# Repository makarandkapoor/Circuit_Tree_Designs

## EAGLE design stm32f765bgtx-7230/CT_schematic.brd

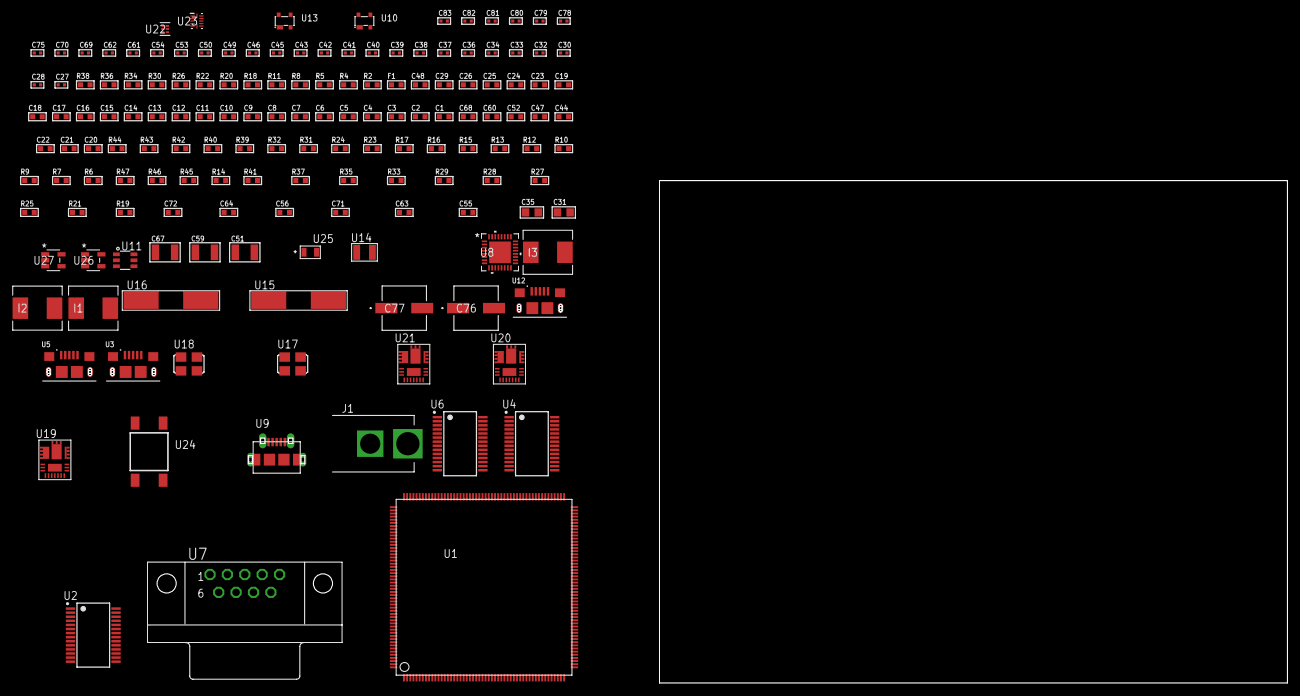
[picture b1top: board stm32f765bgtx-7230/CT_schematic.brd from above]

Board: 2 copper layers, 154 parts (0 on the bottom side), 116 nets, no tracks yet.

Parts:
C1, C24, C29, C48: 1e-06; C0603
C2, C3, C4, C5, C6, C7, C8, C9, C10, C11, C12, C13, C14, C15, C16, C17, C18, C19, C25, C26: 1e-07; C0603
C20: 4.7e-06; C0603
C21, C22, C44, C47, C52, C60, C68: 2.2e-06; C0603
C23: 1e-08; C0603
C27, C28: 1e-11; C0402
C30, C32, C33, C34, C36, C37, C38, C39, C40, C41, C42, C43, C45, C46, C53, C54, C61, C62, C69, C70, C75, C79, C81: 1e-07; C0402
C31, C35: 4.7e-06; C0805
C49, C50, C78, C80, C82, C83: 1e-08; C0402
C51, C59, C67: 0.0001; C1210
C55, C63, C71: 8.5935703950126e-09; R0603
C56, C64, C72: 2.929626271027e-07; R0603
C76, C77: 0.0001; EXV-9H
F1: 240.0; L0603
I1, I2, I3: 6.8e-07; IND25X25CZ
J1: PJ-037B; PJ-037B_PACKAGE
R2: 1000.0; R0603
R4, R5, R8, R11: 4700.0; R0603
R6, R7, R9, R10, R12, R13, R16, R17, R42, R43: 10000.0; R0603
R14: 100000.0; R0603
R15: 47000.0; R0603
R18, R26, R34: 0.1; R0603
R19, R27, R35: 4030.2416170974; R0603
R20: 1600.0; R0603
R21, R29, R37: 59.319518072289; R0603
R22, R30, R38: 130.0; R0603
R23, R31, R39: 39000.0; R0603
R24, R32, R40: 49900.0; R0603
R25, R33, R41: 5216.2133333333; R0603
R28: 719.68600305311; R0603
R36: 453.0; R0603
R44: 82000.0; R0603
R45: 300000.0; R0603
R46: 120000.0; R0603
R47: 200000.0; R0603
U1: STM32F765BGT6; LQFP208
U2, U4: FT232RL-REEL; SSOP-28
U3, U5, U12: 10118193-0001LF; FCI_10118193-0001LF
U6: ST3241EBPR; SSOP-28
U7: 182-009-113R531; 182-009-MALE
U8: TUSB1210BRHBR; RHB32_3P45X3P45
U9: 47590-0001; MICRO_USB_AB
U10, U13: prtr5v0u2ax; SOT143B
U11: MAX4995AAUT+T; SOT-23-6
U14: ABS07-32.768KHZ-7-T
U15, U16: ABLS-12.000MHZ-B4-T
U17: ASFL1-19.2MHZ-NCS; ASFL1
U18: ASFL1-25MHZ-NCS; ASFL1
U19, U20, U21: IR3899MTR1PBF
U22: TPS3895ADRYR; SON-6
U23: LSF0204DRUTR; RUT0012A
U24: 4-1437565-2; SW_4-1437565-2
U25: Q65110A2395; LGM67K-G1J2-24-Z
U26, U27: nc7sz125m5x; NC7SZ125M5X

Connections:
CLK_CRYSTAL_U1_9: C27.1, U1.9, U14.1
CLK_CRYSTAL_U1_10: C28.1, U1.10, U14.2
CLK_CRYSTAL_U2_27: U2.27, U15.1
CLK_CRYSTAL_U2_28: U2.28, U15.2
CLK_CRYSTAL_U4_27: U4.27, U16.1
CLK_CRYSTAL_U4_28: U4.28, U16.2
CLK_U1_32: U1.32, U18.3
CLK_U8_1: U8.1, U17.3
GND: C1.2, C2.2, C3.2, C4.2, C5.2, C6.2, C7.2, C8.2, C9.2, C10.2, C11.2, C12.2, C13.2, C14.2, C15.2, C16.2, C17.2, C18.2, C19.2, C20.2, C21.2, C22.2, C23.2, C24.2, C25.2, C26.2, C27.2, C28.2, C29.2, C30.2, C31.2, C32.2, C33.2, C34.2, C35.2, C36.2, C37.2, C38.2, C41.2, C42.2, C43.2, C44.2, C45.2, C46.2, C47.2, C48.2, C49.2, C50.2, C52.2, C53.2, C54.2, C60.2, C61.2, C62.2, C68.2, C69.2, C70.2, C75.2, C76.2, C77.2, C78.2, C79.2, C80.2, C81.2, C82.2, C83.2, J1.2, R2.2, R6.2, R10.2, R13.2, R15.2, R17.2, R18.1, R18.2, R20.2, R23.2, R25.2, R26.1, R26.2, R28.2, R31.2, R33.2, R34.1, R34.2, R36.2, R39.2, R41.2, R44.2, R46.2, U1.14, U1.25, U1.40, U1.51, U1.60, U1.72, U1.82, U1.93, U1.114, U1.125, U1.136, U1.145, U1.149, U1.170, U1.184, U1.202, U2.7, U2.18, U2.21, U2.25, U2.26, U3.5, U3.6, U3.7, U3.8, U3.9, U4.7, U4.18, U4.21, U4.25, U4.26, U5.5, U5.6, U5.7, U5.8, U5.9, U6.23, U6.25, U7.5, U8.33, U9.5, U9.6, U9.7, U9.8, U9.9, U10.1, U11.2, U12.5, U12.6, U12.7, U12.8, U12.9, U13.1, U17.2, U18.2, U19.4, U19.11, U19.17, U20.4, U20.11, U20.17, U21.4, U21.11, U21.17, U22.2, U23.6, U25.C, U26.1, U26.3, U27.1, U27.3
NET_U1_34: R4.1, U1.34, U26.4
NET_U1_42: C23.1, C24.1, F1.1, U1.41, U1.42
NET_U1_92: C21.1, U1.92
NET_U1_148: C22.1, U1.148
NET_U1_197: R6.1, U1.197
NET_U1_203: R7.1, U1.203
NET_U1_208: U24.3, U24.4
NET_U2_14: R9.1, U2.14
NET_U2_17: C32.1, U2.17
NET_U2_19: R10.1, U2.19
NET_U3_1: R8.1, U3.1
NET_U3_2: U2.16, U3.2
NET_U3_3: U2.15, U3.3
NET_U4_14: R12.1, U4.14
NET_U4_17: C36.1, U4.17
NET_U4_19: R13.1, U4.19
NET_U5_1: R11.1, U5.1
NET_U5_2: U4.16, U5.2
NET_U5_3: U4.15, U5.3
NET_U6_1: C40.1, U6.1
NET_U6_2: C40.2, U6.2
NET_U6_3: C42.1, U6.3
NET_U6_22: R14.1, U6.22
NET_U6_24: C39.2, U6.24
NET_U6_27: C41.1, U6.27
NET_U6_28: C39.1, U6.28
NET_U7_2: U6.4, U7.2
NET_U7_3: U6.9, U7.3
NET_U7_7: U6.5, U7.7
NET_U7_8: U6.10, U7.8
NET_U8_11: R16.1, U8.11
NET_U8_12: C47.1, U8.12
NET_U8_14: R17.1, U8.14
NET_U8_20: C44.1, U8.20
NET_U8_27: R5.1, U8.27, U27.4
NET_U9_1: C48.1, U8.22, U9.1, U10.4, U11.1
NET_U9_2: U8.19, U9.2, U10.3
NET_U9_3: U8.18, U9.3, U10.2
NET_U9_4: U8.23, U9.4
NET_U11_3: R15.1, U11.3
NET_U11_4: U8.17, U11.4
NET_U19_1: C55.1, R19.1, R20.1, R21.1, R22.1, U19.1, U19.8
NET_U19_2: C54.1, U19.2
NET_U19_3: C55.2, C56.1, C56.2, U19.3
NET_U19_5: R23.1, U19.5
NET_U19_10: C52.1, U19.10
NET_U19_12: C51.1, I1.1, U19.12
NET_U19_14: C51.2, U19.14
NET_U19_15: R24.1, R25.1, U19.15
NET_U19_ATNET_3: I1.2, R19.2
NET_U19_ATNET_4: C56.2, R21.2
NET_U20_1: C63.1, R27.1, R28.1, R29.1, R30.1, U20.1, U20.8
NET_U20_2: C62.1, U20.2
NET_U20_3: C63.2, C64.1, C64.2, U20.3
NET_U20_5: R31.1, U20.5
NET_U20_10: C60.1, U20.10
NET_U20_12: C59.1, I2.1, U20.12
NET_U20_14: C59.2, U20.14
NET_U20_15: R32.1, R33.1, U20.15
NET_U20_ATNET_3: I2.2, R27.2
NET_U20_ATNET_4: C64.2, R29.2
NET_U21_1: C71.1, R35.1, R36.1, R37.1, R38.1, U21.1, U21.8
NET_U21_2: C70.1, U21.2
NET_U21_3: C71.2, C72.1, C72.2, U21.3
NET_U21_5: R39.1, U21.5
NET_U21_10: C68.1, U21.10
NET_U21_12: C67.1, I3.1, U21.12
NET_U21_14: C67.2, U21.14
NET_U21_15: R40.1, R41.1, U21.15
NET_U21_ATNET_3: I3.2, R35.2
NET_U21_ATNET_4: C72.2, R37.2
NET_U22_1: R43.1, R44.1, U22.1
NET_U22_3: R45.2, R46.1, U22.3
NET_U22_4: R42.1, U22.4, U26.2, U27.2
NET_U23_12: R47.1, U23.12
NET_U24_1: R2.1, U24.1, U24.2
PROC_UART4_CTS: U1.107, U2.3
PROC_UART4_RTS: U1.106, U2.11
PROC_UART4_RX: U1.11, U2.1
PROC_UART4_TX: U1.43, U2.5
PROC_UART5_CTS: U1.141, U4.3
PROC_UART5_RTS: U1.140, U4.11
PROC_UART5_RX: U1.166, U4.1
PROC_UART5_TX: U1.163, U4.5
PROC_UART7_CTS_TOXCVR: U6.13, U23.9
PROC_UART7_RTS_TOXCVR: U6.18, U23.8
PROC_UART7_RX_TOXCVR: U6.19, U23.7
PROC_UART7_TX_TOXCVR: U6.14, U23.10
PROC_USB_OTG_FS_DM: U1.145, U12.2, U13.3
PROC_USB_OTG_FS_DP: U1.146, U12.3, U13.2
PROC_USB_OTG_FS_VBUS: C29.1, U1.143, U12.1, U13.4
PROC_USB_OTG_HS_ULPI_CK: U1.54, U8.26
PROC_USB_OTG_HS_ULPI_D0: U1.50, U8.3
PROC_USB_OTG_HS_ULPI_D1: U1.61, U8.4
PROC_USB_OTG_HS_ULPI_D2: U1.62, U8.5
PROC_USB_OTG_HS_ULPI_D3: U1.90, U8.6
PROC_USB_OTG_HS_ULPI_D4: U1.91, U8.7
PROC_USB_OTG_HS_ULPI_D5: U1.104, U8.9
PROC_USB_OTG_HS_ULPI_D6: U1.105, U8.10
PROC_USB_OTG_HS_ULPI_D7: U1.194, U8.13
PROC_USB_OTG_HS_ULPI_DIR: U1.13, U8.31
PROC_USB_OTG_HS_ULPI_NXT: U1.38, U8.2
PROC_USB_OTG_HS_ULPI_STP: U1.35, U8.29
VCC_S1_16V6: C53.1, C61.1, C69.1, C76.1, C77.1, J1.1, R24.2, R32.2, R40.2, U19.9, U20.9, U21.9
VCC_TIER1_1V8: C1.1, C2.1, C3.1, C4.1, C5.1, C6.1, C7.1, C8.1, C9.1, C10.1, C11.1, C12.1, C13.1, C14.1, C15.1, C16.1, C17.1, C18.1, C19.1, C20.1, C25.1, C26.1, C33.1, C37.1, C45.1, C46.1, C75.1, C80.1, C81.1, C82.1, C83.1, F1.2, I1.2, R4.2, R5.2, R7.2, R16.2, R19.2, R42.2, R43.2, R45.1, R47.2, U1.6, U1.15, U1.26, U1.39, U1.52, U1.59, U1.73, U1.83, U1.94, U1.103, U1.115, U1.124, U1.137, U1.150, U1.158, U1.171, U1.185, U1.204, U2.4, U4.4, U8.28, U8.30, U8.32, U22.6, U23.1, U26.5, U27.5
VCC_TIER1_3V3: C30.1, C31.1, C34.1, C35.1, C38.1, C43.1, C49.1, C50.1, C78.1, C79.1, I2.2, R9.2, R12.2, R14.2, R27.2, U2.20, U4.20, U6.26, U8.21, U17.4, U18.4, U23.11
VCC_TIER1_5V0: I3.2, R35.2, U11.5

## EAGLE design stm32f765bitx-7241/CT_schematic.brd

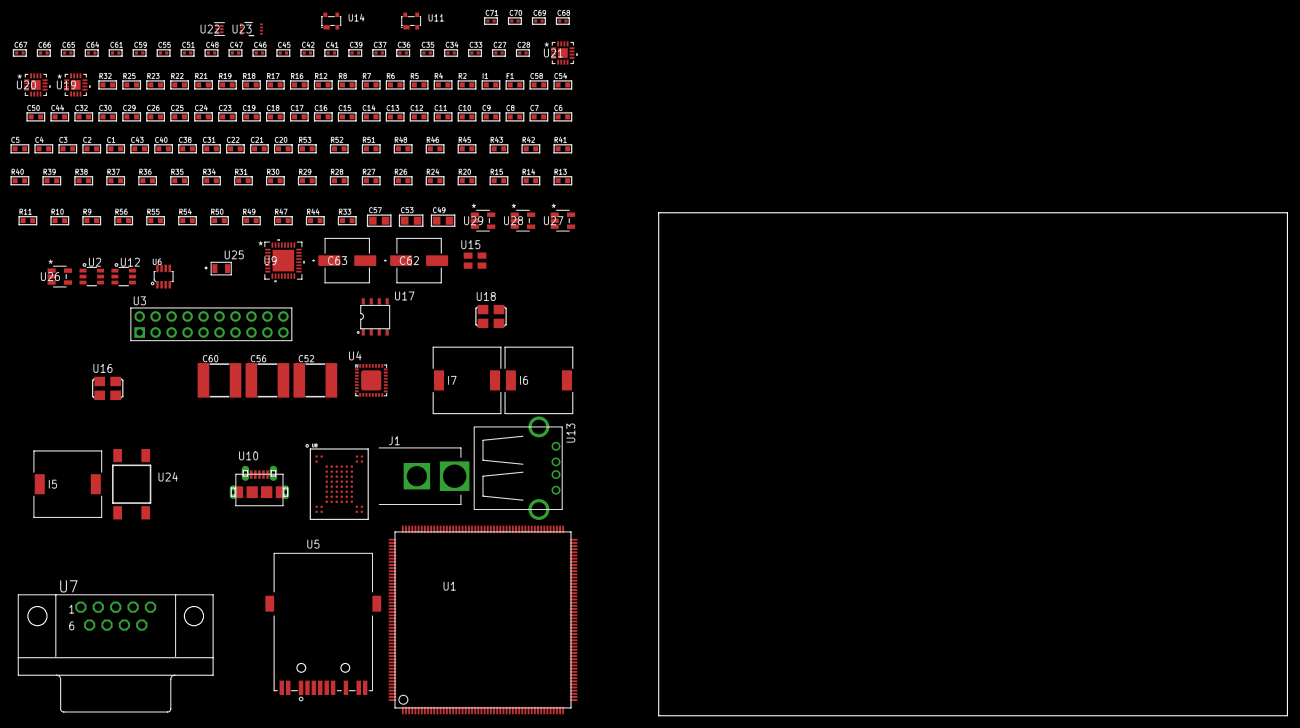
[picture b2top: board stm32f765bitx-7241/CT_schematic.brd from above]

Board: 2 copper layers, 160 parts (0 on the bottom side), 127 nets, no tracks yet.

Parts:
C1, C24, C29, C30, C32, C44, C50, C54, C58: 1e-06; C0603
C2, C3, C4, C5, C6, C7, C8, C9, C10, C11, C12, C13, C14, C15, C16, C17, C18, C19, C25, C26: 1e-07; C0603
C20: 4.7e-06; C0603
C21, C22, C38, C40, C43: 2.2e-06; C0603
C23: 1e-08; C0603
C27, C33, C34, C35, C36, C37, C39, C41, C42, C51, C55, C59, C61, C65, C67: 1e-07; C0402
C28: 2.2e-08; C0402
C31: 4.7e-10; C0603
C45, C46, C47, C48, C64, C66, C68, C69, C70, C71: 1e-08; C0402
C49, C53, C57: 1e-05; C0805
C52, C56, C60: 6.8e-05; 2220
C62, C63: 0.0001; EXV-9H
F1: 240.0; L0603
I1: 97.0; R0603
I5, I6: 2.5e-06; DR1040
I7: 3.8e-06; DR1040
J1: PJ-037B; PJ-037B_PACKAGE
R2: 1000.0; R0603
R4, R5, R6: 4700.0; R0603
R7, R8: 2200.0; R0603
R9, R39: 47000.0; R0603
R10, R11, R13, R14, R15, R24, R26, R27, R28, R29, R30, R31, R34, R35, R36, R37, R38, R40, R41, R51, R52: 10000.0; R0603
R12: 1270.0; R0603
R16, R17: 0.1; R0603
R18, R19: 200.0; R0603
R20: 12100.0; R0603
R21, R22, R23, R25: 49.9; R0603
R32: 120.0; R0603
R33: 100000.0; R0603
R42, R45, R48: 20000.0; R0603
R43: 39000.0; R0603
R44, R47, R50, R54: 300000.0; R0603
R46: 91000.0; R0603
R49: 150000.0; R0603
R53: 82000.0; R0603
R55: 120000.0; R0603
R56: 200000.0; R0603
U1: STM32F765BIT6; LQFP208
U2, U12: MAX4995AAUT+T; SOT-23-6
U3: TST-110-05-T-D-RA
U4: LAN8710AI-EZK; QFN-32
U5: 7498011122R
U6: MAX3051EKA+T; SOT-23-8
U7: 182-009-113R531; 182-009-MALE
U8: mt29f4g08abbdah4; VFBGA-63
U9: TUSB1210BRHBR; RHB32_3P45X3P45
U10: 47590-0001; MICRO_USB_AB
U11, U14: prtr5v0u2ax; SOT143B
U13: 61400416021; USB-A-H
U15: ASEK-32.768KHz-ECST; ASEK
U16: ASFL1-25MHZ-NCS; ASFL1
U17: idt74fct38072; IDT74FCT38072
U18: ASFL1-26MHZ-NCS; ASFL1
U19, U20, U21: LTC3601EUD#PBF; QFN-16_EP
U22: TPS3895ADRYR; SON-6
U23: LSF0102DCTR; DCU0008A_N
U24: 4-1437565-2; SW_4-1437565-2
U25: Q65110A2395; LGM67K-G1J2-24-Z
U26, U27, U28, U29: nc7sz125m5x; NC7SZ125M5X

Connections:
CLK_U1_9: U1.9, U15.3
CLK_U1_32: U1.32, U17.7
CLK_U4_5: U4.5, U17.6
CLK_U9_1: U9.1, U18.3
CLK_U17_3: U16.3, U17.3
GND: C1.2, C2.2, C3.2, C4.2, C5.2, C6.2, C7.2, C8.2, C9.2, C10.2, C11.2, C12.2, C13.2, C14.2, C15.2, C16.2, C17.2, C18.2, C19.2, C20.2, C21.2, C22.2, C23.2, C24.2, C25.2, C26.2, C27.2, C28.2, C29.2, C30.2, C31.2, C32.2, C33.2, C34.2, C35.2, C36.2, C37.2, C38.2, C39.2, C40.2, C41.2, C42.2, C43.2, C44.2, C45.2, C46.2, C47.2, C48.2, C49.2, C50.2, C52.1, C52.2, C53.2, C54.2, C56.1, C56.2, C57.2, C58.2, C60.1, C60.2, C61.2, C62.2, C63.2, C64.2, C65.2, C66.2, C67.2, C68.2, C69.2, C70.2, C71.2, J1.2, R2.2, R9.2, R10.2, R12.2, R14.2, R16.2, R17.2, R18.2, R20.2, R30.2, R31.2, R33.2, R39.2, R42.2, R44.2, R45.2, R47.2, R48.2, R50.2, R53.2, R55.2, U1.14, U1.25, U1.40, U1.51, U1.60, U1.72, U1.82, U1.93, U1.114, U1.125, U1.136, U1.149, U1.170, U1.184, U1.202, U2.2, U3.4, U3.6, U3.8, U3.10, U3.12, U3.14, U3.16, U3.18, U3.20, U4.EXP, U5.10, U6.2, U7.5, U8.C5, U8.F7, U8.K3, U8.K8, U9.33, U10.5, U10.6, U10.7, U10.8, U10.9, U11.1, U12.2, U13.4, U13.5, U13.6, U14.1, U15.2, U16.2, U17.4, U17.5, U17.8, U18.2, U19.1, U19.9, U19.17, U20.1, U20.9, U20.17, U21.1, U21.9, U21.17, U22.2, U23.1, U25.C, U26.2, U26.3, U27.1, U27.3, U28.1, U28.3, U29.1, U29.3
NET_U1_34: R5.1, U1.34, U28.4
NET_U1_36: R7.1, U1.36, U4.17
NET_U1_42: C23.1, C24.1, F1.1, U1.41, U1.42
NET_U1_45: R8.1, U1.45, U4.16
NET_U1_92: C21.1, U1.92
NET_U1_144: R12.1, U1.144
NET_U1_148: C22.1, U1.148
NET_U1_197: R10.1, U1.197
NET_U1_203: R11.1, U1.203
NET_U1_208: U24.3, U24.4
NET_U2_3: R9.1, U2.3
NET_U4_1: C29.1, I1.1, R21.2, R22.2, R23.2, R25.2, U4.1, U4.27
NET_U4_6: C30.1, C31.1, U4.6
NET_U4_18: R24.1, U4.18
NET_U4_19: R4.1, U4.19, U27.4
NET_U4_32: R20.1, U4.32
NET_U5_1: R21.1, U4.29, U5.1
NET_U5_3: R19.2, R22.1, U4.28, U5.3
NET_U5_4: R23.1, U4.31, U5.4
NET_U5_5: C28.1, U5.2, U5.5
NET_U5_6: R25.1, U4.30, U5.6
NET_U5_8: R17.1, U5.8
NET_U5_9: R19.1, U5.9
NET_U5_11: U4.2, U5.11
NET_U5_12: R18.1, U5.12
NET_U5_13: R16.1, U5.13, U5.14
NET_U6_6: R32.2, U6.6
NET_U6_8: R33.1, U6.8
NET_U7_2: R32.2, U6.6, U7.2
NET_U7_3: R32.1, U6.7, U7.3
NET_U8_C3: R38.1, U8.C3
NET_U9_11: R40.1, U9.11
NET_U9_12: C43.1, U9.12
NET_U9_14: R41.1, U9.14
NET_U9_20: C40.1, U9.20
NET_U9_27: R6.1, U9.27, U29.4
NET_U10_1: C44.1, U9.22, U10.1, U11.4, U12.1
NET_U10_2: U9.19, U10.2, U11.3
NET_U10_3: U9.18, U10.3, U11.2
NET_U10_4: U9.23, U10.4
NET_U12_3: R39.1, U12.3
NET_U12_4: U9.17, U12.4
NET_U19_3: C51.2, I5.1, U19.3, U19.4
NET_U19_6: C51.1, U19.6
NET_U19_7: C50.1, U19.7, U19.12
NET_U19_10: R44.1, U19.10
NET_U19_11: R42.1, R43.1, U19.11
NET_U19_ATNET_3: I5.2, R43.2
NET_U20_3: C55.2, I6.1, U20.3, U20.4
NET_U20_6: C55.1, U20.6
NET_U20_7: C54.1, U20.7, U20.12
NET_U20_10: R47.1, U20.10
NET_U20_11: R45.1, R46.1, U20.11
NET_U20_ATNET_3: I6.2, R46.2
NET_U21_3: C59.2, I7.1, U21.3, U21.4
NET_U21_6: C59.1, U21.6
NET_U21_7: C58.1, U21.7, U21.12
NET_U21_10: R50.1, U21.10
NET_U21_11: R48.1, R49.1, U21.11
NET_U21_ATNET_3: I7.2, R49.2
NET_U22_1: R52.1, R53.1, U22.1
NET_U22_3: R54.2, R55.1, U22.3
NET_U22_4: R51.1, U22.4, U26.4, U27.2, U28.2, U29.2
NET_U23_8: R56.1, U23.8
NET_U24_1: R2.1, U24.1, U24.2
PROC_CAN1_RX_TOXCVR: U6.4, U23.5
PROC_CAN1_TX_TOXCVR: U6.1, U23.6
PROC_ETH_COL: R28.1, U1.47, U4.15
PROC_ETH_CRS: U1.43, U4.14
PROC_ETH_RXD0: R26.1, U1.57, U4.11
PROC_ETH_RXD1: R27.1, U1.58, U4.10
PROC_ETH_RXD2: U1.96, U4.9
PROC_ETH_RXD3: R31.1, U1.97, U4.8
PROC_ETH_RX_CLK: R30.1, U1.44, U4.7
PROC_ETH_RX_DV: U1.56, U4.26
PROC_ETH_RX_ER: R29.1, U1.12, U4.13
PROC_ETH_TXD0: U1.182, U4.22
PROC_ETH_TXD1: U1.183, U4.23
PROC_ETH_TXD2: U1.37, U4.24
PROC_ETH_TXD3: U1.1, U4.25
PROC_ETH_TX_CLK: U1.38, U4.20
PROC_ETH_TX_EN: U1.180, U4.21
PROC_FMC_A16: U1.111, U8.D5
PROC_FMC_A17: U1.112, U8.C4
PROC_FMC_D0: U1.116, U8.H4
PROC_FMC_D1: U1.117, U8.J4
PROC_FMC_D2: U1.164, U8.K4
PROC_FMC_D3: U1.165, U8.K5
PROC_FMC_D4: U1.79, U8.K6
PROC_FMC_D5: U1.80, U8.J7
PROC_FMC_D6: U1.81, U8.K7
PROC_FMC_D7: U1.84, U8.J8
PROC_FMC_INT: R34.1, U1.134, U8.C8
PROC_FMC_NCE: R35.1, U1.140, U8.C6
PROC_FMC_NOE: R37.1, U1.168, U8.D4
PROC_FMC_NWE: R36.1, U1.169, U8.C7
PROC_GPIO_TO_U1_USB_FAULT: R13.1, U1.3, U2.6
PROC_GPIO_TO_U1_VBUS_EN: R14.1, U1.2, U2.4
PROC_SYS_JTCK_SWCLK: U1.159, U3.9
PROC_SYS_JTDO_SWO: U1.192, U3.13
PROC_SYS_JTMS_SWDIO: U1.147, U3.7
PROC_USB_OTG_FS_DM: U1.145, U13.2, U14.3
PROC_USB_OTG_FS_DP: U1.146, U13.3, U14.2
PROC_USB_OTG_FS_VBUS: U1.143, U2.1, U13.1, U14.4
PROC_USB_OTG_HS_ULPI_CK: U1.54, U9.26
PROC_USB_OTG_HS_ULPI_D0: U1.50, U9.3
PROC_USB_OTG_HS_ULPI_D1: U1.61, U9.4
PROC_USB_OTG_HS_ULPI_D2: U1.62, U9.5
PROC_USB_OTG_HS_ULPI_D3: U1.90, U9.6
PROC_USB_OTG_HS_ULPI_D4: U1.91, U9.7
PROC_USB_OTG_HS_ULPI_D5: U1.104, U9.9
PROC_USB_OTG_HS_ULPI_D6: U1.105, U9.10
PROC_USB_OTG_HS_ULPI_D7: U1.194, U9.13
PROC_USB_OTG_HS_ULPI_DIR: U1.13, U9.31
PROC_USB_OTG_HS_ULPI_NXT: U1.48, U9.2
PROC_USB_OTG_HS_ULPI_STP: U1.35, U9.29
RST_OUT_U3_SRESET_B: R15.1, U3.15, U26.1
VCC_S1_7V4: C49.1, C53.1, C57.1, C62.1, C63.1, J1.1, U19.15, U19.16, U20.15, U20.16, U21.15, U21.16
VCC_TIER1_1V8: C1.1, C2.1, C3.1, C4.1, C5.1, C6.1, C7.1, C8.1, C9.1, C10.1, C11.1, C12.1, C13.1, C14.1, C15.1, C16.1, C17.1, C18.1, C19.1, C20.1, C25.1, C26.1, C27.1, C32.1, C34.1, C35.1, C36.1, C37.1, C38.1, C41.1, C42.1, C52.2, C61.1, C66.1, C67.1, C68.1, C69.1, C70.1, C71.1, F1.2, I5.2, R4.2, R5.2, R6.2, R7.2, R8.2, R11.2, R13.2, R15.2, R24.2, R26.2, R27.2, R28.2, R29.2, R34.2, R35.2, R36.2, R37.2, R38.2, R40.2, R41.2, R43.2, R51.2, R52.2, R54.1, U1.6, U1.15, U1.26, U1.39, U1.52, U1.59, U1.73, U1.83, U1.94, U1.103, U1.115, U1.124, U1.137, U1.150, U1.158, U1.171, U1.185, U1.204, U3.1, U4.12, U8.D3, U8.G4, U8.H8, U8.J6, U9.28, U9.30, U9.32, U19.8, U22.6, U23.2, U26.5, U27.5, U28.5, U29.5
VCC_TIER1_3V3: C33.1, C39.1, C45.1, C46.1, C47.1, C48.1, C56.2, C64.1, C65.1, I1.2, I6.2, R46.2, R56.2, U6.3, U9.21, U15.4, U16.4, U17.1, U17.2, U18.4, U20.8, U23.7
VCC_TIER1_5V0: C60.2, I7.2, R49.2, U2.5, U12.5, U21.8

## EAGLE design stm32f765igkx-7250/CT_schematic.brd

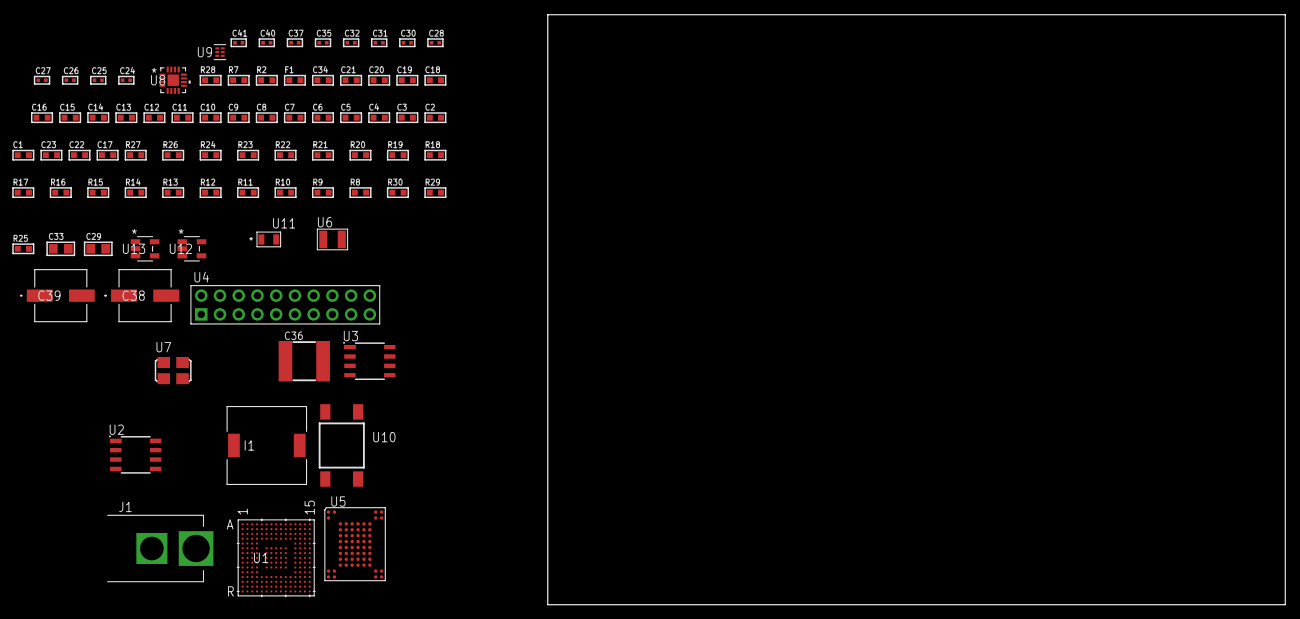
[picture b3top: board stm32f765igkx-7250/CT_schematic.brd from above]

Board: 2 copper layers, 100.0 x 80.0 mm, 82 parts (0 on the bottom side), 55 nets, no tracks yet.

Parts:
C1, C19, C34: 1e-06; C0603
C2, C3, C4, C5, C6, C7, C8, C9, C10, C11, C12, C13, C14, C15, C16, C20, C21: 1e-07; C0603
C17: 4.7e-06; C0603
C18: 1e-08; C0603
C22, C23: 2.2e-06; C0603
C24, C25: 1e-11; C0402
C26, C27, C32, C40, C41: 1e-08; C0402
C28, C30, C31, C35, C37: 1e-07; C0402
C29, C33: 1e-05; C0805
C36: 6.8e-05; 2220
C38, C39: 0.0001; EXV-9H
F1: 240.0; L0603
I1: 3.8e-06; DR1040
J1: PJ-037B; PJ-037B_PACKAGE
R2: 1000.0; R0603
R7: 4700.0; R0603
R8, R9, R10, R11, R12, R13, R14, R15, R16, R17, R18, R19, R20, R21, R22, R26, R27: 10000.0; R0603
R23: 20000.0; R0603
R24: 91000.0; R0603
R25: 300000.0; R0603
R28: 9100.0; R0603
R29: 680000.0; R0603
R30: 120000.0; R0603
U1: STM32F765IGK6; UFBGA176_25
U2: AT25040B-SSHL-T; SOIC-8
U3: AT25M02-SSHD-T; SOIC-8
U4: TST-110-05-T-D-RA
U5: TH58NVG3S0HBAI4
U6: ABS07-32.768KHZ-7-T
U7: ASFL1-25MHZ-NCS; ASFL1
U8: LTC3601EUD#PBF; QFN-16_EP
U9: TPS3895ADRYR; SON-6
U10: 4-1437565-2; SW_4-1437565-2
U11: Q65110A2395; LGM67K-G1J2-24-Z
U12, U13: nc7sz125m5x; NC7SZ125M5X

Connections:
CLK_CRYSTAL_U1_E1: C24.1, U1.E1, U6.1
CLK_CRYSTAL_U1_F1: C25.1, U1.F1, U6.2
CLK_U1_G1: U1.G1, U7.3
GND: C1.2, C2.2, C3.2, C4.2, C5.2, C6.2, C7.2, C8.2, C9.2, C10.2, C11.2, C12.2, C13.2, C14.2, C15.2, C16.2, C17.2, C18.2, C19.2, C20.2, C21.2, C22.2, C23.2, C24.2, C25.2, C26.2, C27.2, C28.2, C29.2, C30.2, C31.2, C32.2, C33.2, C34.2, C36.1, C36.2, C37.2, C38.2, C39.2, C40.2, C41.2, J1.2, R2.2, R8.2, R10.2, R23.2, R25.2, R28.2, R30.2, U1.D5, U1.D7, U1.D8, U1.D9, U1.F2, U1.F6, U1.F7, U1.F8, U1.F9, U1.F10, U1.F12, U1.G2, U1.G6, U1.G7, U1.G8, U1.G9, U1.G10, U1.G12, U1.H6, U1.H7, U1.H8, U1.H9, U1.H10, U1.H12, U1.J6, U1.J7, U1.J8, U1.J9, U1.J10, U1.K6, U1.K7, U1.K8, U1.K9, U1.K10, U1.M1, U1.M8, U1.M9, U1.N1, U2.4, U3.4, U4.4, U4.6, U4.8, U4.10, U4.12, U4.14, U4.16, U4.18, U4.20, U5.C5, U5.K3, U5.K8, U7.2, U8.1, U8.9, U8.17, U9.2, U11.C, U12.2, U12.3, U13.1, U13.3
NET_U1_C6: R9.1, U1.C6
NET_U1_D6: R8.1, U1.D6
NET_U1_F13: C23.1, U1.F13
NET_U1_J1: R7.1, U1.J1, U13.4
NET_U1_L4: R10.1, U1.L4
NET_U1_M10: C22.1, U1.M10
NET_U1_R1: C18.1, C19.1, F1.1, U1.P1, U1.R1
NET_U1_R15: U10.3, U10.4
NET_U2_3: R11.1, U2.3
NET_U2_7: R13.1, U2.7
NET_U3_3: R14.1, U3.3
NET_U3_7: R16.1, U3.7
NET_U5_C3: R21.1, U5.C3
NET_U8_3: C35.2, I1.1, U8.3, U8.4
NET_U8_6: C35.1, U8.6
NET_U8_7: C34.1, U8.7, U8.12
NET_U8_10: R25.1, U8.10
NET_U8_11: R23.1, R24.1, U8.11
NET_U8_ATNET_3: I1.2, R24.2
NET_U9_1: R27.1, R28.1, U9.1
NET_U9_3: R29.2, R30.1, U9.3
NET_U9_4: R26.1, U9.4, U12.4, U13.2
NET_U10_1: R2.1, U10.1, U10.2
PROC_FMC_A16: U1.N14, U5.D5
PROC_FMC_A17: U1.N13, U5.C4
PROC_FMC_D0: U1.M14, U5.H4
PROC_FMC_D1: U1.L14, U5.J4
PROC_FMC_D2: U1.B12, U5.K4
PROC_FMC_D3: U1.C12, U5.K5
PROC_FMC_D4: U1.R8, U5.K6
PROC_FMC_D5: U1.P8, U5.J7
PROC_FMC_D6: U1.P9, U5.K7
PROC_FMC_D7: U1.R9, U5.J8
PROC_FMC_INT: R22.1, U1.J14, U5.C8
PROC_FMC_NCE: R18.1, U1.C10, U5.C6
PROC_FMC_NOE: R19.1, U1.D10, U5.D4
PROC_FMC_NWE: R20.1, U1.C11, U5.C7
PROC_SPI1_MISO: U1.A9, U2.2
PROC_SPI1_MOSI: U1.A6, U2.5
PROC_SPI1_NSS: R12.1, U1.A13, U2.1
PROC_SPI1_SCK: U1.B9, U2.6
PROC_SPI2_MISO: U1.C14, U3.2
PROC_SPI2_MOSI: U1.C13, U3.5
PROC_SPI2_NSS: R15.1, U1.B4, U3.1
PROC_SPI2_SCK: U1.B15, U3.6
PROC_SYS_JTCK_SWCLK: U1.A14, U4.9
PROC_SYS_JTDO_SWO: U1.A10, U4.13
PROC_SYS_JTMS_SWDIO: U1.A15, U4.7
RST_OUT_U4_SRESET_B: R17.1, U4.15, U12.1
VCC_S1_7V4: C33.1, C38.1, C39.1, J1.1, U8.15, U8.16
VCC_TIER1_3V3: C1.1, C2.1, C3.1, C4.1, C5.1, C6.1, C7.1, C8.1, C9.1, C10.1, C11.1, C12.1, C13.1, C14.1, C15.1, C16.1, C17.1, C20.1, C21.1, C26.1, C27.1, C28.1, C29.1, C30.1, C31.1, C32.1, C36.2, C37.1, C40.1, C41.1, F1.2, I1.2, R7.2, R9.2, R11.2, R12.2, R13.2, R14.2, R15.2, R16.2, R17.2, R18.2, R19.2, R20.2, R21.2, R22.2, R24.2, R26.2, R27.2, R29.1, U1.C1, U1.C5, U1.C7, U1.C8, U1.C9, U1.F3, U1.G3, U1.G13, U1.H13, U1.J12, U1.J13, U1.K4, U1.N8, U1.N9, U1.N10, U2.8, U3.8, U4.1, U5.H8, U5.J6, U7.4, U8.8, U9.6, U12.5, U13.5

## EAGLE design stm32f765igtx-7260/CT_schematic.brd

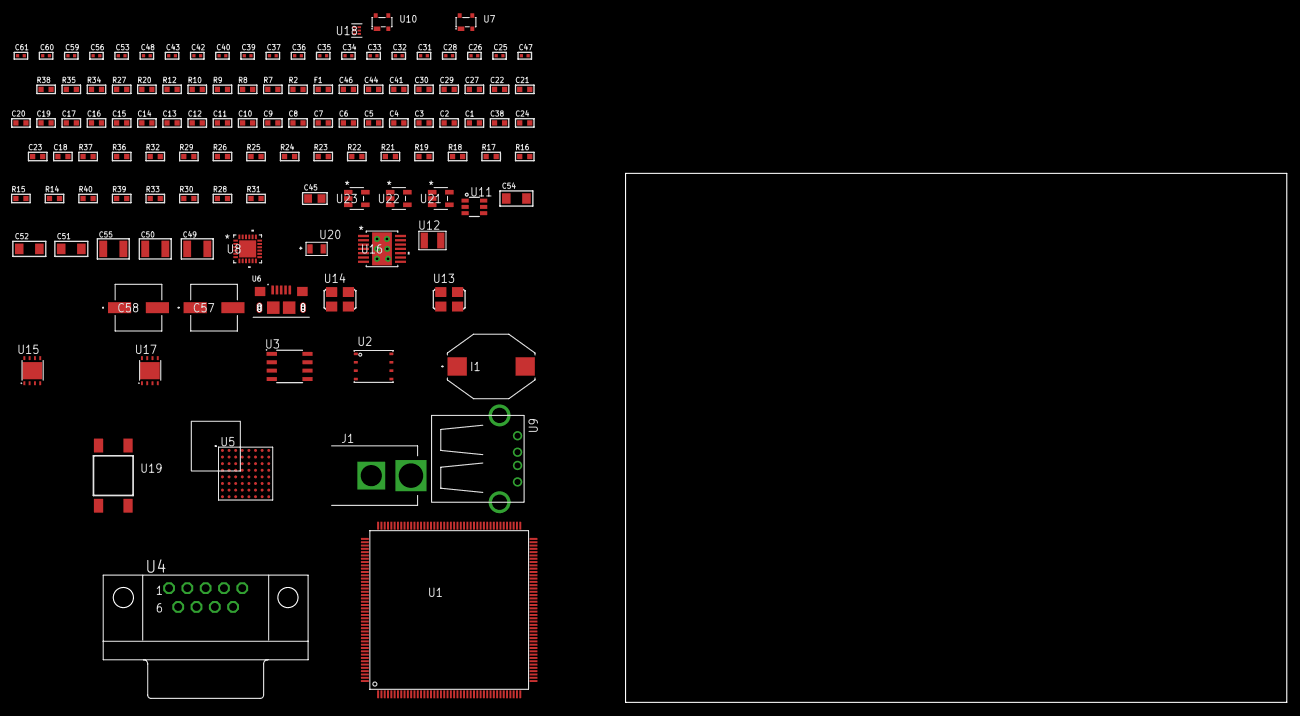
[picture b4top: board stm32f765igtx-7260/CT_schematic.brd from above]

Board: 2 copper layers, 120 parts (0 on the bottom side), 114 nets, no tracks yet.

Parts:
C1, C20, C27, C29, C30, C44, C46: 1e-06; C0603
C2, C3, C4, C5, C6, C7, C8, C9, C10, C11, C12, C13, C14, C15, C16, C17, C21, C22: 1e-07; C0603
C18: 4.7e-06; C0603
C19: 1e-08; C0603
C23, C24, C38: 2.2e-06; C0603
C25, C26: 1e-11; C0402
C28, C32, C34, C36, C37, C39, C40, C42, C43, C53, C59, C60, C61: 1e-08; C0402
C31, C33, C35, C48, C56: 1e-07; C0402
C41: 0.0001; R0603
C45: 1e-05; C0805
C47: 3.3e-09; C0402
C49, C50: 2.2e-05; C1210
C51, C52, C54: 1e-05; C1206
C55: 1e-05; C1210
C57, C58: 0.0001; EXV-9H
F1: 240.0; L0603
I1: 1e-05; IND_PM3316
J1: PJ-037B; PJ-037B_PACKAGE
R2, R35: 1000.0; R0603
R7, R8, R9: 4700.0; R0603
R10, R12: 2200.0; R0603
R14, R15, R16, R17, R18, R19, R21, R22, R23, R24, R25, R36, R37: 10000.0; R0603
R20: 120.0; R0603
R26: 47000.0; R0603
R27: 8060.0; R0603
R28, R30, R33: 100000.0; R0603
R29: 36000.0; R0603
R31: 71007.101651032; R0603
R32: 22000.0; R0603
R34: 3900.0; R0603
R38: 9100.0; R0603
R39: 680000.0; R0603
R40: 120000.0; R0603
U1: STM32F765IGT6; LQFP176
U2: 24AA512-I/MF; DFN8-S
U3: MCP2562-E/SN; SOIC-8
U4: 182-009-113R531; 182-009-MALE
U5: PC28F512P33BFD
U6: 10118193-0001LF; FCI_10118193-0001LF
U7, U10: prtr5v0u2ax; SOT143B
U8: USB3317C-CP-TR; QFN-24
U9: 61400416021; USB-A-H
U11: MAX4995AAUT+T; SOT-23-6
U12: ABS07-32.768KHZ-7-T
U13: ASFL1-25MHZ-NCS; ASFL1
U14: ASFL1-26MHZ-NCS; ASFL1
U15: LP2951ACSDX/NOPB; WSON-8
U16: tps54225PWP; HTSSOP14
U17: LP3878SDX-ADJ/NOPB; WSON-8
U18: TPS3895ADRYR; SON-6
U19: 4-1437565-2; SW_4-1437565-2
U20: Q65110A2395; LGM67K-G1J2-24-Z
U21, U22, U23: nc7sz125m5x; NC7SZ125M5X

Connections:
CLK_CRYSTAL_U1_9: C25.1, U1.9, U12.1
CLK_CRYSTAL_U1_10: C26.1, U1.10, U12.2
CLK_U1_29: U1.29, U13.3
CLK_U8_23: U8.23, U14.3
GND: C1.2, C2.2, C3.2, C4.2, C5.2, C6.2, C7.2, C8.2, C9.2, C10.2, C11.2, C12.2, C13.2, C14.2, C15.2, C16.2, C17.2, C18.2, C19.2, C20.2, C21.2, C22.2, C23.2, C24.2, C25.2, C26.2, C27.2, C28.2, C29.2, C30.2, C31.2, C32.2, C33.2, C34.2, C35.2, C36.2, C37.2, C38.2, C39.2, C40.2, C41.2, C42.2, C43.2, C44.2, C45.2, C46.2, C47.2, C49.2, C50.2, C51.2, C52.2, C53.2, C54.2, C55.2, C56.2, C57.2, C58.2, C59.2, C60.2, C61.2, J1.2, R2.2, R14.2, R16.2, R17.2, R18.2, R26.2, R27.2, R30.2, R32.2, R35.2, R38.2, R40.2, U1.14, U1.22, U1.37, U1.61, U1.71, U1.90, U1.102, U1.113, U1.122, U1.126, U1.135, U1.148, U1.158, U2.4, U3.2, U3.8, U4.5, U5.B2, U5.H2, U5.H4, U5.H6, U6.5, U6.6, U6.7, U6.8, U6.9, U7.1, U8.1, U8.25, U9.4, U9.5, U9.6, U10.1, U11.2, U13.2, U14.2, U15.3, U15.4, U15.PAD, U16.5, U16.8, U16.9, U16.15, U17.3, U17.PAD, U18.2, U20.C, U21.1, U21.3, U22.1, U22.3, U23.1, U23.3
NET_U1_31: R8.1, U1.31, U22.4
NET_U1_39: C19.1, C20.1, F1.1, U1.38, U1.39
NET_U1_48: R16.1, U1.48
NET_U1_81: C23.1, U1.81
NET_U1_125: C24.1, U1.125
NET_U1_164: R10.1, U1.164, U2.6
NET_U1_166: R14.1, U1.166
NET_U1_168: R12.1, U1.168, U2.5
NET_U1_171: R15.1, U1.171
NET_U1_176: U19.3, U19.4
NET_U2_1: R17.1, U2.1
NET_U2_2: R18.1, U2.2
NET_U2_3: R19.1, U2.3
NET_U3_6: R20.2, U3.6
NET_U4_2: R20.2, U3.6, U4.2
NET_U4_3: R20.1, U3.7, U4.3
NET_U5_A4: C35.1, C36.1, U5.A4
NET_U5_C6: R24.1, U5.C6
NET_U5_D4: R7.1, U5.D4, U21.4
NET_U8_4: C38.1, U8.4
NET_U8_22: R9.1, U8.22, U23.4
NET_U8_24: R27.1, U8.24
NET_U9_1: C41.1, U8.2, U9.1, U10.4, U11.1
NET_U9_2: U8.5, U9.2, U10.3
NET_U9_3: U8.6, U9.3, U10.2
NET_U11_3: R26.1, U11.3
NET_U11_4: U8.7, U11.4
NET_U15_5: R28.1, U15.5
NET_U15_7: R29.2, R30.1, U15.7
NET_U16_2: R31.2, R32.1, U16.2
NET_U16_3: C46.1, U16.3
NET_U16_4: C47.1, U16.4
NET_U16_10: C48.1, I1.1, U16.10, U16.11
NET_U16_12: C48.2, U16.12
NET_U17_1: C53.1, U17.1
NET_U17_6: R34.2, R35.1, U17.6
NET_U17_8: R33.1, U17.8
NET_U18_1: R37.1, R38.1, U18.1
NET_U18_3: R39.2, R40.1, U18.3
NET_U18_4: R36.1, U18.4, U21.2, U22.2, U23.2
NET_U19_1: R2.1, U19.1, U19.2
PROC_CAN1_RX: U1.11, U3.4
PROC_CAN1_TX: U1.128, U3.1
PROC_FMC_A0: U1.16, U5.A1
PROC_FMC_A1: U1.17, U5.B1
PROC_FMC_A2: U1.18, U5.C1
PROC_FMC_A3: U1.19, U5.D1
PROC_FMC_A4: U1.20, U5.D2
PROC_FMC_A5: U1.21, U5.A2
PROC_FMC_A6: U1.60, U5.C2
PROC_FMC_A7: U1.63, U5.A3
PROC_FMC_A8: U1.64, U5.B3
PROC_FMC_A9: U1.65, U5.C3
PROC_FMC_A10: U1.66, U5.D3
PROC_FMC_A11: U1.67, U5.C4
PROC_FMC_A12: U1.106, U5.A5
PROC_FMC_A13: U1.107, U5.B5
PROC_FMC_A14: U1.108, U5.C5
PROC_FMC_A15: U1.109, U5.D7
PROC_FMC_A16: U1.99, U5.D8
PROC_FMC_A17: U1.100, U5.A7
PROC_FMC_A18: U1.101, U5.B7
PROC_FMC_A19: U1.2, U5.C7
PROC_FMC_A20: U1.3, U5.C8
PROC_FMC_A21: U1.4, U5.A8
PROC_FMC_A22: U1.5, U5.G1
PROC_FMC_A23: U1.1, U5.H8
PROC_FMC_A24: U1.156, U5.B6
PROC_FMC_CLK: U1.145, U5.E6
PROC_FMC_D0: U1.104, U5.F2
PROC_FMC_D1: U1.105, U5.E2
PROC_FMC_D2: U1.142, U5.G3
PROC_FMC_D3: U1.143, U5.E4
PROC_FMC_D4: U1.68, U5.E5
PROC_FMC_D5: U1.69, U5.G5
PROC_FMC_D6: U1.70, U5.G6
PROC_FMC_D7: U1.73, U5.H7
PROC_FMC_D8: U1.74, U5.E1
PROC_FMC_D9: U1.75, U5.E3
PROC_FMC_D10: U1.76, U5.F3
PROC_FMC_D11: U1.77, U5.F4
PROC_FMC_D12: U1.78, U5.F5
PROC_FMC_D13: U1.96, U5.H5
PROC_FMC_D14: U1.97, U5.G7
PROC_FMC_D15: U1.98, U5.E7
PROC_FMC_NE2: R22.1, U1.117, U5.B4
PROC_FMC_NL: R21.1, U1.165, U5.F6
PROC_FMC_NOE: R23.1, U1.146, U5.F8
PROC_FMC_NWAIT: U1.115, U5.F7
PROC_FMC_NWE: R25.1, U1.147, U5.G8
PROC_USB_OTG_FS_DM: U1.122, U6.2, U7.3
PROC_USB_OTG_FS_DP: U1.123, U6.3, U7.2
PROC_USB_OTG_FS_VBUS: C27.1, U1.120, U6.1, U7.4
PROC_USB_OTG_HS_ULPI_CK: U1.51, U8.12
PROC_USB_OTG_HS_ULPI_D0: U1.47, U8.16
PROC_USB_OTG_HS_ULPI_D1: U1.56, U8.15
PROC_USB_OTG_HS_ULPI_D2: U1.57, U8.14
PROC_USB_OTG_HS_ULPI_D3: U1.79, U8.13
PROC_USB_OTG_HS_ULPI_D4: U1.80, U8.11
PROC_USB_OTG_HS_ULPI_D5: U1.92, U8.10
PROC_USB_OTG_HS_ULPI_D6: U1.93, U8.9
PROC_USB_OTG_HS_ULPI_D7: U1.163, U8.8
PROC_USB_OTG_HS_ULPI_DIR: U1.13, U8.19
PROC_USB_OTG_HS_ULPI_NXT: U1.35, U8.18
PROC_USB_OTG_HS_ULPI_STP: U1.32, U8.20
VCC_S1_10V6: C44.1, C51.1, C52.1, C54.1, C57.1, C58.1, J1.1, R33.2, U15.8, U16.7, U16.13, U16.14, U17.4
VCC_TIER1_1V8: C40.1, C45.1, C59.1, C60.1, C61.1, R28.2, R29.1, U8.21, U15.1, U21.5, U22.5, U23.5
VCC_TIER1_3V3: C1.1, C2.1, C3.1, C4.1, C5.1, C6.1, C7.1, C8.1, C9.1, C10.1, C11.1, C12.1, C13.1, C14.1, C15.1, C16.1, C17.1, C18.1, C21.1, C22.1, C28.1, C30.1, C31.1, C32.1, C33.1, C34.1, C37.1, C39.1, C42.1, C43.1, C49.1, C50.1, C56.1, F1.2, I1.2, R7.2, R8.2, R9.2, R10.2, R12.2, R15.2, R19.2, R21.2, R22.2, R23.2, R24.2, R25.2, R31.1, R36.2, R37.2, R39.1, U1.6, U1.15, U1.23, U1.36, U1.49, U1.62, U1.72, U1.82, U1.91, U1.103, U1.114, U1.127, U1.136, U1.149, U1.159, U1.172, U2.7, U2.8, U3.5, U5.A6, U5.D5, U5.D6, U5.G4, U5.H3, U8.3, U8.17, U13.4, U14.4, U16.1, U18.6
VCC_TIER1_5V0: C29.1, C55.1, R34.1, U3.3, U11.5, U17.5
